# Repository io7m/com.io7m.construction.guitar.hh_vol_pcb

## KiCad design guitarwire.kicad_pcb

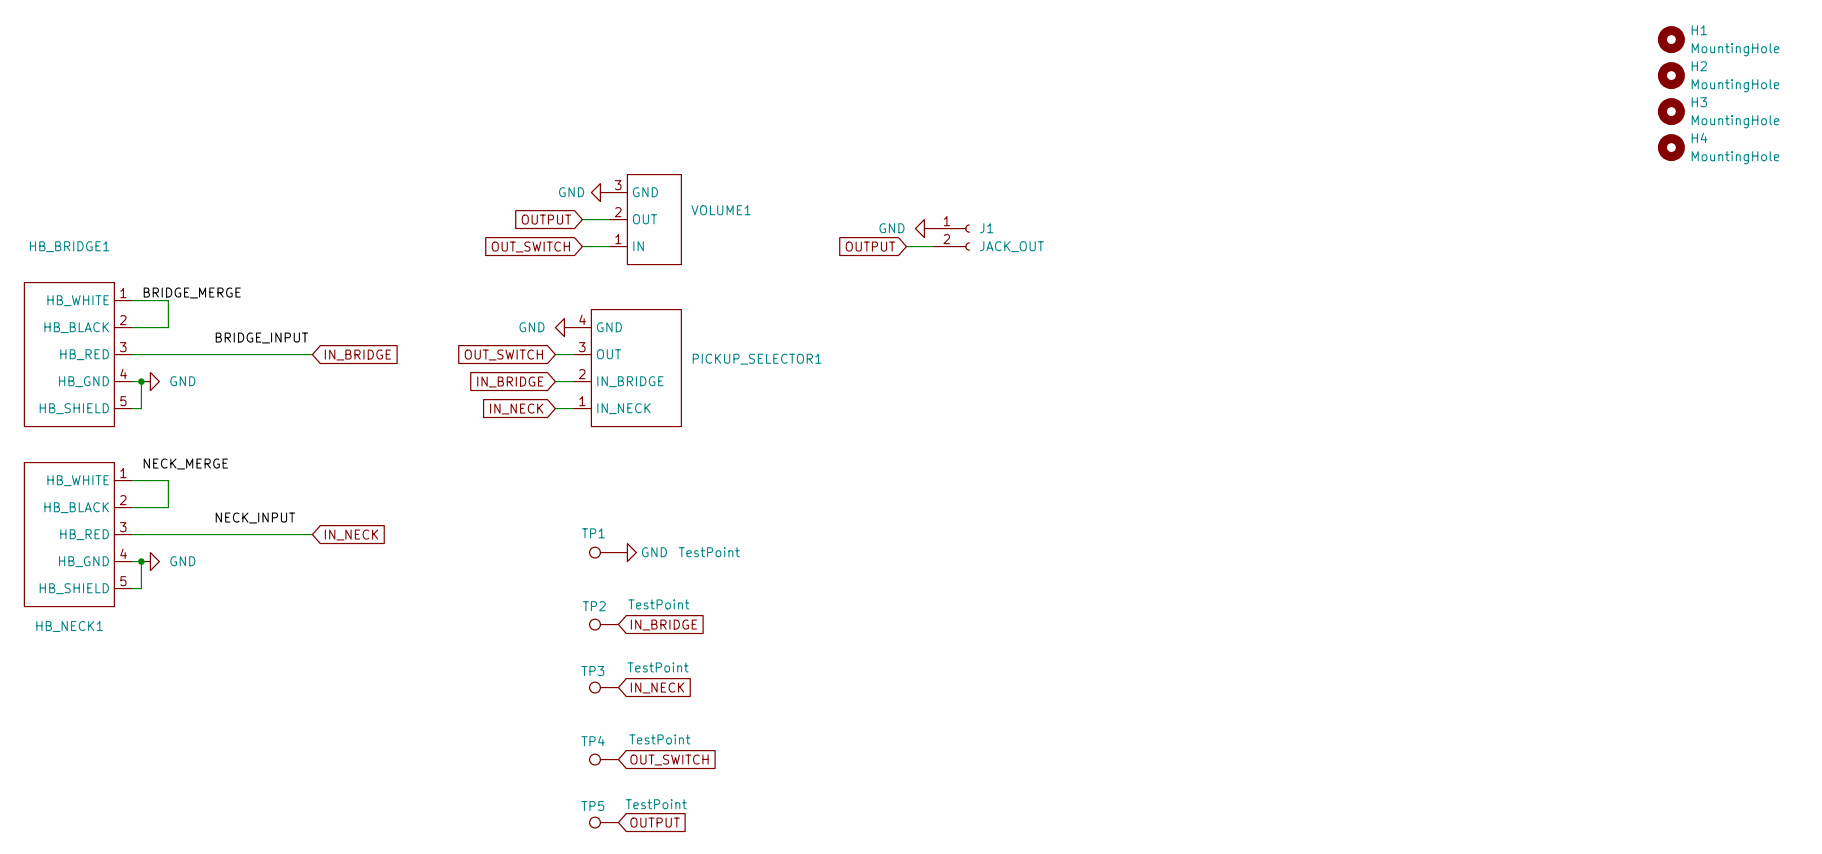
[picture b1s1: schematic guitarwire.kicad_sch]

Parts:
H1, H2, H3, H4: MountingHole; MountingHole_2.7mm_M2.5
HB_BRIDGE1: JST_XH_B5B-XH-AM_1x05_P2.50mm_Vertical
HB_NECK1: JST_XH_B5B-XH-AM_1x05_P2.50mm_Vertical
J1: JACK_OUT; JST_XH_B2B-XH-AM_1x02_P2.50mm_Vertical
PICKUP_SELECTOR1: JST_XH_B4B-XH-AM_1x04_P2.50mm_Vertical
TP1, TP2, TP3, TP4, TP5: TestPoint; TestPoint_THTPad_2.0x2.0mm_Drill1.0mm
VOLUME1: JST_XH_B3B-XH-AM_1x03_P2.50mm_Vertical

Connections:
/BRIDGE_MERGE: HB_BRIDGE1.1 (HB_WHITE), HB_BRIDGE1.2 (HB_BLACK)
GND: HB_BRIDGE1.4 (HB_GND), HB_BRIDGE1.5 (HB_SHIELD), HB_NECK1.4 (HB_GND), HB_NECK1.5 (HB_SHIELD), J1.1, PICKUP_SELECTOR1.4 (GND), TP1.1, VOLUME1.3 (GND)
IN_BRIDGE: HB_BRIDGE1.3 (HB_RED), PICKUP_SELECTOR1.2 (IN_BRIDGE), TP2.1
IN_NECK: HB_NECK1.3 (HB_RED), PICKUP_SELECTOR1.1 (IN_NECK), TP3.1
unnamed: HB_NECK1.1 (HB_WHITE), HB_NECK1.2 (HB_BLACK)
OUTPUT: J1.2, TP5.1, VOLUME1.2 (OUT)
OUT_SWITCH: PICKUP_SELECTOR1.3 (OUT), TP4.1, VOLUME1.1 (IN)

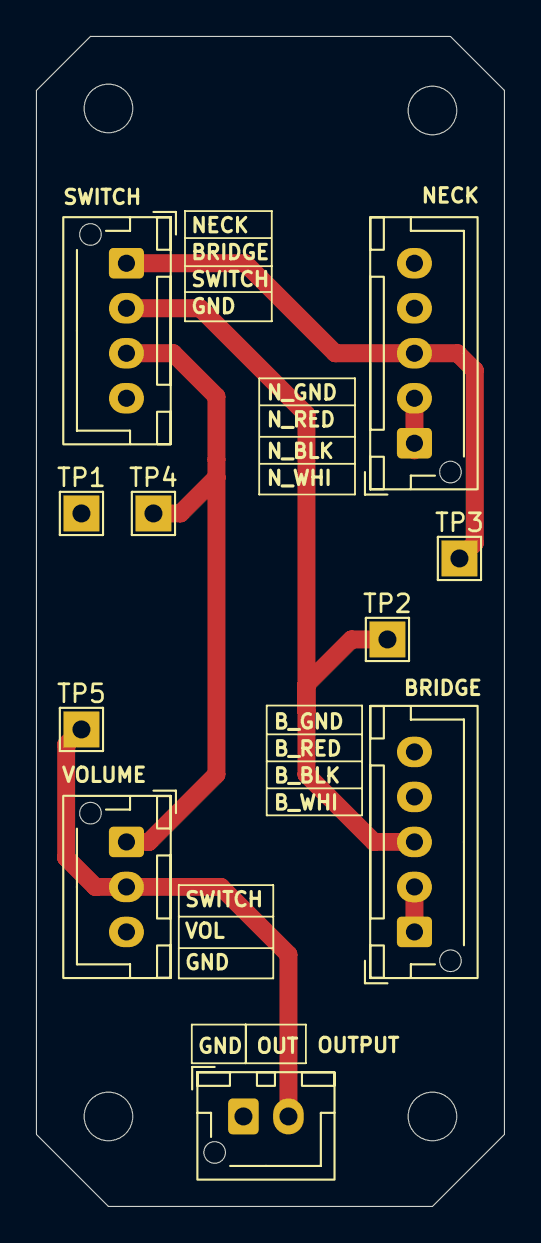
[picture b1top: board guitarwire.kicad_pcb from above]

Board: 2 copper layers, 26.0 x 65.0 mm, 14 parts (0 on the bottom side), 7 nets.

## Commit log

2025-11-15 Initial version.
2025-11-15 Export gerbers.
2026-02-02 Redesign board to use JST XH connectors.
